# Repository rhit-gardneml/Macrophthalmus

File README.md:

"# Macrophthalmus"
This is an ece capstone team at rose-hulman makeing a communication module for LEO communication 

Remember to pull before you start working!

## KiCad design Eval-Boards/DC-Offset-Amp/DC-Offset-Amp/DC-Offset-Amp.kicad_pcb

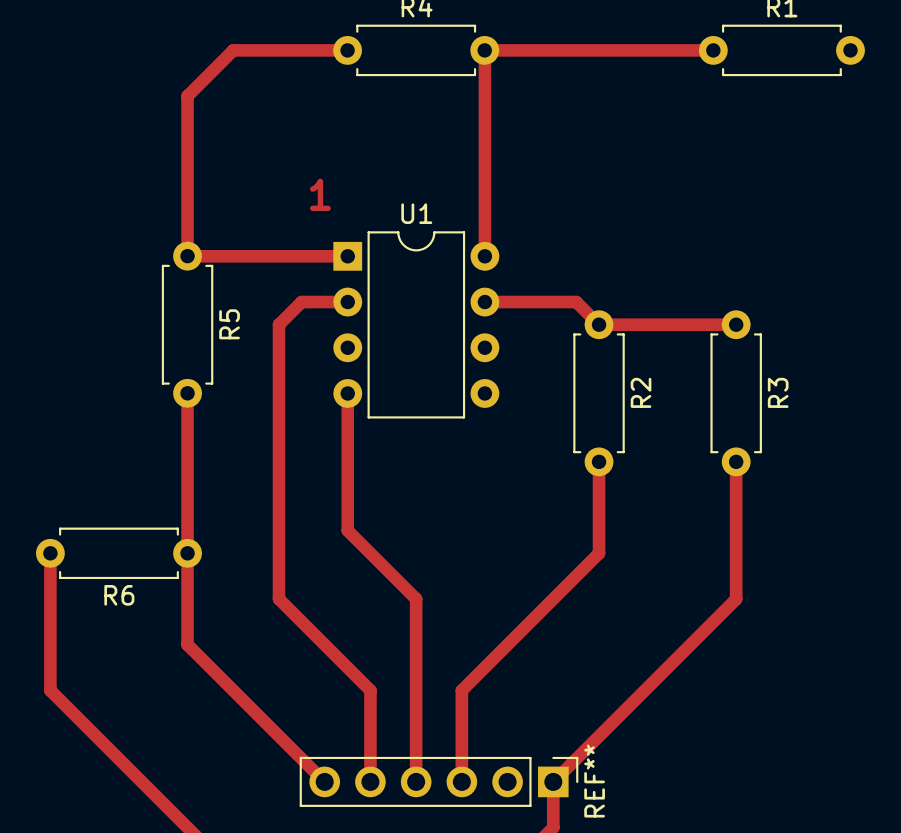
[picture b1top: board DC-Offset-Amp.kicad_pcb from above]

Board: 2 copper layers, 7 parts (0 on the bottom side), 2 nets.

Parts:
R1, R2, R3, R4, R5, R6: R; R_Axial_DIN0207_L6.3mm_D2.5mm_P7.62mm_Horizontal
U1: LM380N-8; DIP-8_W7.62mm

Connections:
unnamed: R1.1, R4.2, U1.8 (BYPASS)
unnamed: R2.1, R3.1, U1.7 (VS)

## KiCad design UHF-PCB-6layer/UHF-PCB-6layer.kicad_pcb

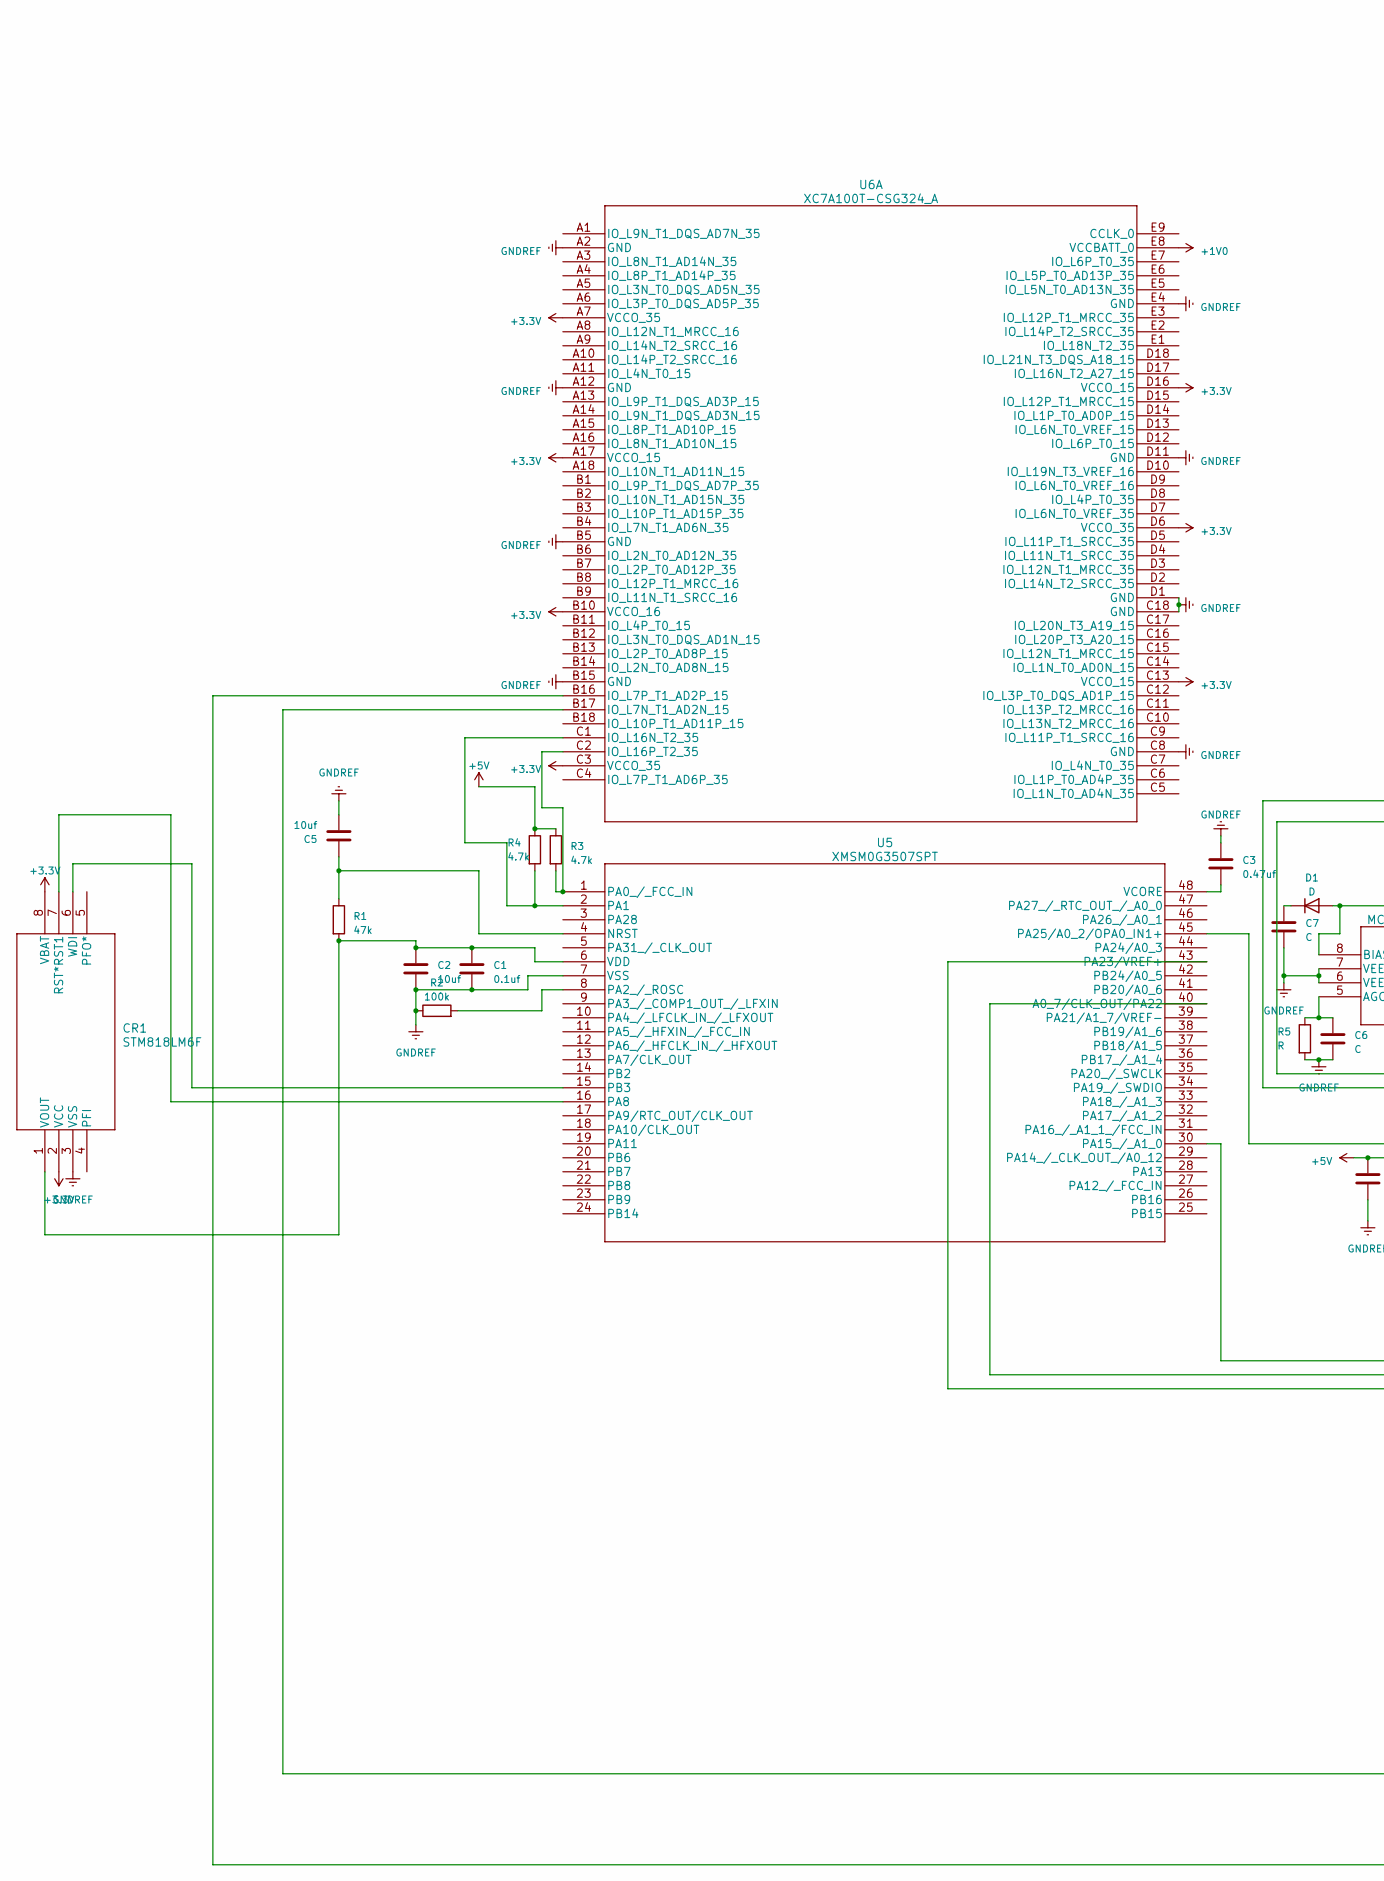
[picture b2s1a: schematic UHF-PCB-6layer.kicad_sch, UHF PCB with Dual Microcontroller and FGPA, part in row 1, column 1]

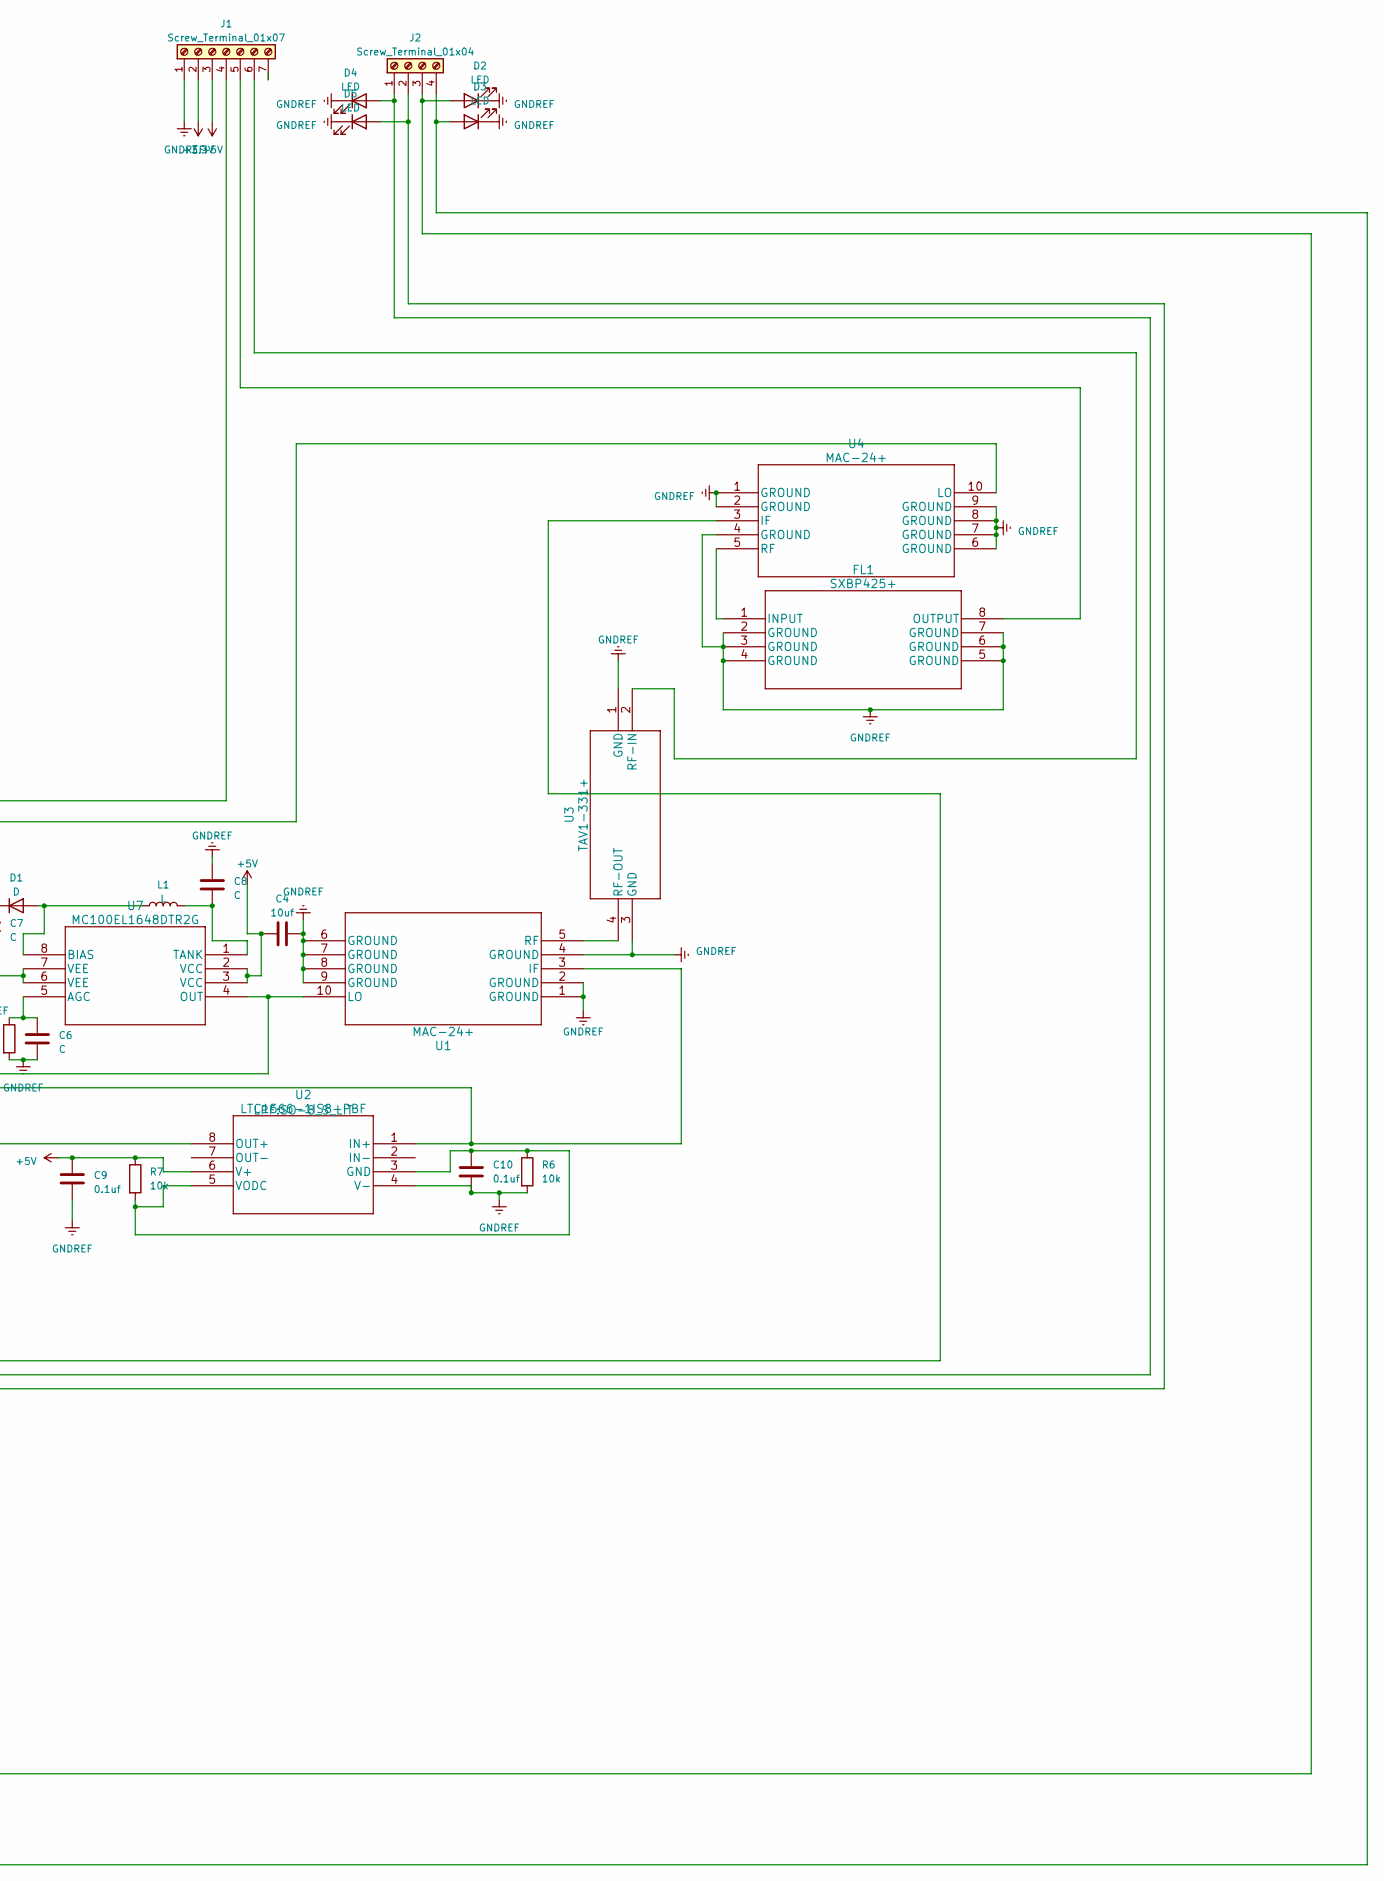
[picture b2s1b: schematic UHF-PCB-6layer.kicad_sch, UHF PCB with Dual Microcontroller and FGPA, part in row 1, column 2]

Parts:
C1, C9, C10: 0.1uf; C_0603_1608Metric
C2, C4, C5: 10uf; C_0603_1608Metric
C3: 0.47uf; C_0603_1608Metric
C6, C7, C8: C; C_0603_1608Metric
CR1: STM818LM6F; SO-8_STM
D1: D; D_0603_1608Metric
D2, D3, D4, D5: LED; LED_2010_5025Metric_Pad1.52x2.65mm_HandSolder
FL1: SXBP425+; HF1139_MNC
J1: Screw_Terminal_01x07; Altech_AK300_1x07_P5.00mm_45-Degree
J2: Screw_Terminal_01x04; Altech_AK300_1x07_P5.00mm_45-Degree
L1: L; L_0603_1608Metric
R1: 47k; R_0603_1608Metric
R2: 100k; R_0603_1608Metric
R3, R4: 4.7k; R_0603_1608Metric
R5: R; R_0603_1608Metric
R6, R7: 10k; R_0603_1608Metric
U1, U4: MAC-24+; DZ1650_MNC
U2: LTC1566-1IS8-PBF; SO-8_S_LIT
U3: TAV1-331+; TE2769_MNC
U5: XMSM0G3507SPT; LQFP48_PT_TEX
U6: XC7A100T-CSG324_A; CS&slash_CSG324_XIL
U7: MC100EL1648DTR2G; TSSOP8_3P10X3P10_ONS

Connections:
+1V0: U6.E8 (VCCBATT_0)
+3.3V: CR1.2 (VCC), CR1.8 (VBAT), J1.2, U6.A7 (VCCO_35), U6.A17 (VCCO_15), U6.B10 (VCCO_16), U6.C3 (VCCO_35), U6.C13 (VCCO_15), U6.D6 (VCCO_35), U6.D16 (VCCO_15)
+5V: C4.2, C9.1, J1.3, R3.1, R4.1, R7.1, U2.6 (V+), U7.2 (VCC), U7.3 (VCC)
GNDREF: C1.1, C2.1, C3.2, C4.1, C5.1, C6.1, C7.2, C8.2, C9.2, C10.2, CR1.3 (VSS), D2.1 (K), D3.1 (K), D4.1 (K), D5.1 (K), FL1.2 (GROUND), FL1.3 (GROUND), FL1.4 (GROUND), FL1.5 (GROUND), FL1.6 (GROUND), FL1.7 (GROUND), J1.1, R2.1, R5.2, R6.2, U1.1 (GROUND), U1.2 (GROUND), U1.4 (GROUND), U1.6 (GROUND), U1.7 (GROUND), U1.8 (GROUND), U1.9 (GROUND), U2.4 (V-), U3.1 (GND), U3.3 (GND), U4.1 (GROUND), U4.2 (GROUND), U4.4 (GROUND), U4.6 (GROUND), U4.7 (GROUND), U4.8 (GROUND), U4.9 (GROUND), U5.7 (VSS), U6.A2 (GND), U6.A12 (GND), U6.B5 (GND), U6.B15 (GND), U6.C8 (GND), U6.C18 (GND), U6.D1 (GND), U6.D11 (GND), U6.E4 (GND), U7.6 (VEE), U7.7 (VEE)
unnamed: CR1.7 (RST*RST1), U5.16 (PA8)
unnamed: C1.2, C2.2, CR1.1 (VOUT), R1.2, U5.6 (VDD)
unnamed: CR1.6 (WDI), U5.15 (PB3)
unnamed: D1.2 (A), L1.1, U7.8 (BIAS)
unnamed: C7.1, D1.1 (K)
unnamed: D2.2 (A), J2.3, U6.B17 (IO_L7N_T1_AD2N_15)
unnamed: D3.2 (A), J2.4, U6.B16 (IO_L7P_T1_AD2P_15)
unnamed: D4.2 (A), J2.1, U5.40 (A0_7/CLK_OUT/PA22)
unnamed: D5.2 (A), J2.2, U5.43 (PA23/VREF+)
unnamed: FL1.1 (INPUT), U4.5 (RF)
unnamed: FL1.8 (OUTPUT), J1.5
unnamed: J1.4, U1.3 (IF), U2.1 (IN+)
unnamed: J1.6, U3.2 (RF-IN)
unnamed: U1.10 (LO), U4.10 (LO), U7.4 (OUT)
unnamed: U1.5 (RF), U3.4 (RF-OUT)
unnamed: C10.1, R6.1, R7.2, U2.3 (GND), U2.5 (VODC)
unnamed: U2.8 (OUT+), U5.45 (PA25/A0_2/OPA0_IN1+)
unnamed: U4.3 (IF), U5.30 (PA15_/_A1_0)
unnamed: C5.2, R1.1, U5.4 (NRST)
unnamed: R3.2, U5.1 (PA0_/_FCC_IN), U6.C2 (IO_L16P_T2_35)
unnamed: R4.2, U5.2 (PA1), U6.C1 (IO_L16N_T2_35)
unnamed: R2.2, U5.8 (PA2_/_ROSC)
unnamed: C3.1, U5.48 (VCORE)
unnamed: C6.2, R5.1, U7.5 (AGC)
unnamed: C8.1, L1.2, U7.1 (TANK)

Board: 2 copper layers, 34 parts (0 on the bottom side), 28 nets, no tracks yet.

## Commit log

2023-10-13 testing setup
2023-10-13 added notebook for rmove
2023-10-13 and they have been removed
2023-10-13 add Channel_Testbook which is a jupyter notebook to simulate AWGN channel for BPSK
2023-10-13 AWGN channel sim added to Channel_Testbook
2023-10-13 hello added
2023-10-14 added BPSK with AWGN channel BER vsEb/No curve plot
2023-11-02 add signalOutline.txt which is outline of signal flow
2023-11-03 step one of signal flow sims, up to bpsk modulation
2023-11-03 need to add BER vs Eb/N0 calculation, and hard desision decoding for demodulation
2023-11-04 added draft of HD decoder, need to make better nouse, var as scalar
2023-11-04 Ideal coherance BPSK demodulation and 200 samples downsampling to convert binary --> bpsk -->AWGN --> square --->binary
2023-11-05 Simulations added and updated, need to add PLL or Castas loop for demodulation, and need to add match filtering with RRC for signalFlow.ipynb
2023-12-15 added pcb folder
2023-12-15 started work on pcb, added FGPA
2023-12-16 added to pcb design, added all comps but mixer and microcontroller
2023-12-17 removed hello.txt
2023-12-17 added microcontroller to schematic
2023-12-18 added XA7A to schematic
2023-12-20 added mixer
2023-12-20 added folder for simulations
2023-12-21 This is test. nothing input
2023-12-21 added matlab and similink files to simulatin folder
2023-12-21 added BOM to datasheets and other
2023-12-21 add start of playing with match filtering
2023-12-21 added not on version control to readme
2023-12-21 moved some stuff around, matlab and simulink simulations now in their folder, same for python
2023-12-21 update to matlab ---> fpga notes
2023-12-21 finished move of stuff
2024-01-02 added required caps and resistors for microcontroller
2024-01-03 added footprints for resistors
2024-01-03 Microcontroller UART
2024-01-03 FPGA UART
2024-01-04 moved stuff around
2024-01-04 changes to pcb
2024-01-04 VCO changed to right module, still need to connect stuff and addd caps + resis + induct
2024-01-05 added more to VCO circuit
2024-01-05 added some gnds
2024-01-08 added connections between FPGA and micro
2024-01-08 maybe some edits idk
2024-01-11 Adding the tests for the mixer.
2024-01-12 This is the Downsample to 2Mhz with a zoom in and a zoom out withe the local oscillator showing
2024-01-13 added pll .m file to repo
2024-01-13 BPSK modultion
    BPSK Modulation
2024-01-13 added wire to schematic
2024-01-13 added Tori BPSK and such
2024-01-13 added 2.3MHz LPF
2024-01-13 added 2.3MHz LPF to input of module
2024-01-13 added connector for power, 3.3v, 5v, gnd, and IF signal
2024-01-15 don't know
2024-01-16 BPSK Simulink Try
    Morrison, Yue-Shan, can you tell me how bad it is?
2024-01-17 bandpass added to lib folder
2024-01-17 added first part of tx side in schematic
2024-01-17 added tx/rx from MC and working on FPGA
2024-01-17 added LEDs and finished of the FPGA
2024-01-17 stuff
2024-01-17 wdt draft added
2024-01-17 draft of SVC added, needs to be vetted
2024-01-17 added new mixer to schematic
2024-01-17 added footprints to all schematic symbols and added to pcb
2024-01-17 this was a change... maybe
2024-01-18 started layout for PCB
2024-01-18 added datasheets
2024-01-19 Add files via upload
    New Bad version not working
2024-01-19 Does this work
    How aobut now?
2024-01-19 added tori BPSK simulink
2024-01-21 Adding the down sample with LNA. Also added up sample from 10->420 MHz
2024-01-21 Adding the tests for the ADC with random PSK signal
2024-01-22 Transmitter Update
    Transciever Module
2024-01-23 Added in DAC code
    UART disabled
2024-01-25 added gbr files and such
2024-01-25 BPSK Reciever
2024-01-25 stuff and board things
2024-01-25 moved BPSK around and changed names
2024-01-25 extracted folder
2024-01-25 Sarah and Tori's HDL from my computer from the QPSK MathWorks module
2024-01-26 added bpf gbr files and eval board schematic
2024-01-26 PARTS
    I added the 1V, 1.8V, and supervisory circuit pcb eval board
2024-01-26 Movin
    Moved eval boards to EVALBOARDS
2024-01-26 Update BP Eval
    Added SMA to BP eval board
2024-01-26 :(
    Finished eval boards
2024-01-29 vco pcb and girber
2024-01-29 added gerber files for VCO
2024-01-29 added name
2024-01-29 VCO Updated
    VCO Fixed
2024-01-29 new bpf pcb
2024-01-30 ADC Code
    ADC code uploaded to GitHub
2024-01-30 something, don't know really what this is
2024-02-04 voc tests
2024-02-07 WDT Scope
    Added WDT Scope Readings
2024-02-10 add mixer data from 2/10 testing
2024-02-10 added data from mixer and BPF
2024-02-10 adc qpsk
    Actual QPSK signal screenshot
2024-02-10 Added Data rate calc
2024-02-19 VCO
    Added change to VOLTAGECONTROLLED Oscillator
2024-03-04 useful document from 310
2024-03-05 Created new board for the Low pass even though it says bandpass stuff
2024-03-06 Fixed the New Low Pass Filter
2024-03-07 New amplifier board
    It looks really bad
2024-03-07 Added BPSK Digital Calculations
2024-03-07 Alot of stuff. Eval board for amp and VCO test
2024-03-08 added dac bpsk
2024-03-11 added back end scope captures
2024-03-13 Mixer board stuff
2024-03-13 AHHHHHHHHHHHH
2024-03-13 ahhhhhh
2024-03-13 Added DAC 100k tests
2024-03-15 pcb grb files added for level shifter, in DC-Offset-Amp
2024-03-15 added drl and such
2024-03-16 added captures from mar 16th
2024-03-17 Added images and adc dma code
2024-03-18 added images
2024-03-19 Updated all MCU code
    Added correct: ADC, DAC, WDT Code
2024-03-19 Added excel files
2024-03-20 Op amp Test
2024-03-22 power amp
2024-03-22 added vna data
2024-04-03 apparently i touched these
